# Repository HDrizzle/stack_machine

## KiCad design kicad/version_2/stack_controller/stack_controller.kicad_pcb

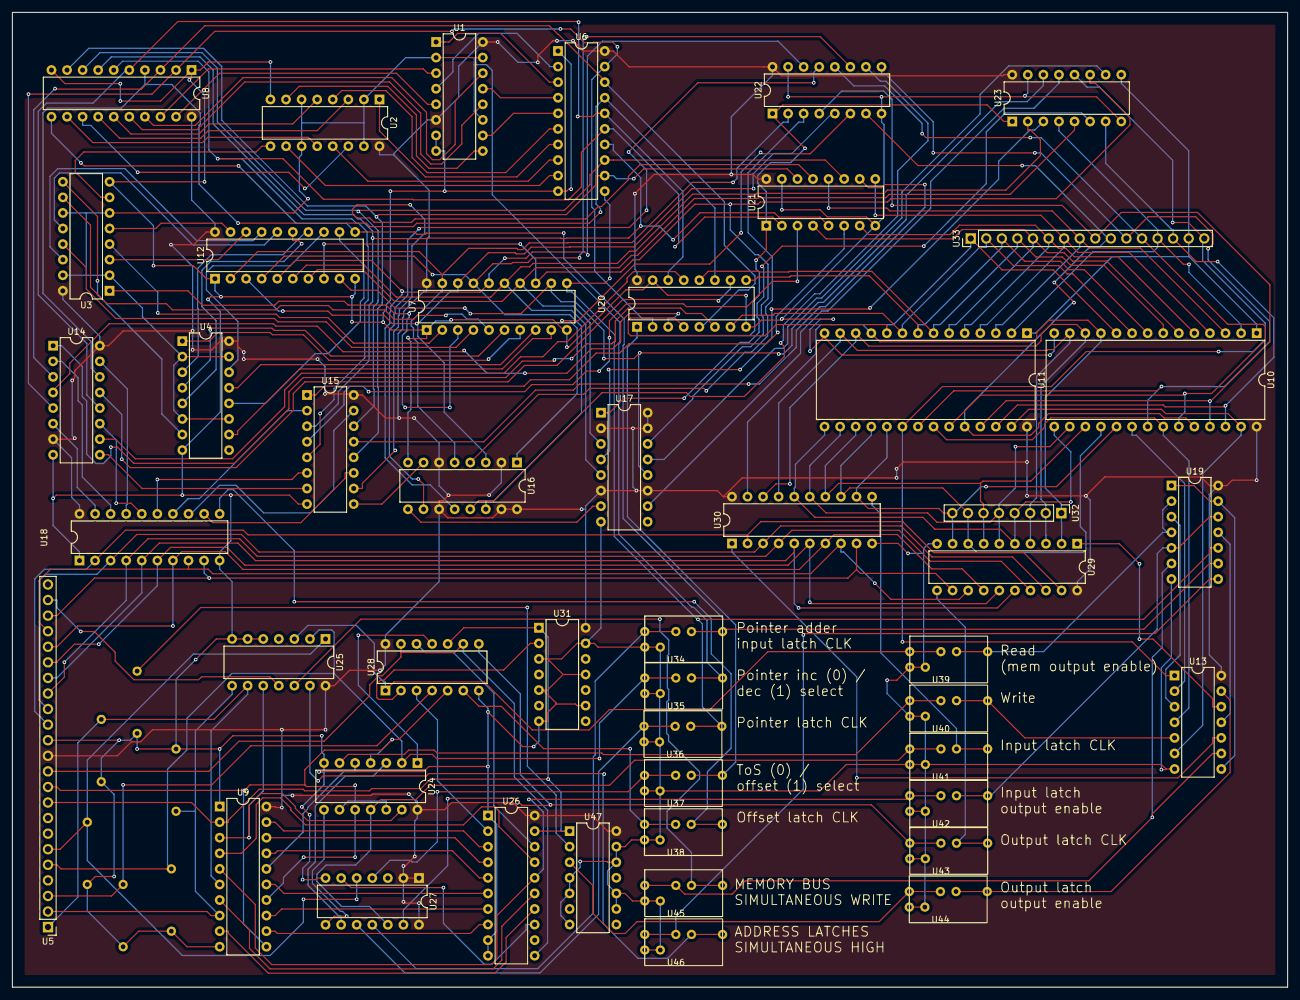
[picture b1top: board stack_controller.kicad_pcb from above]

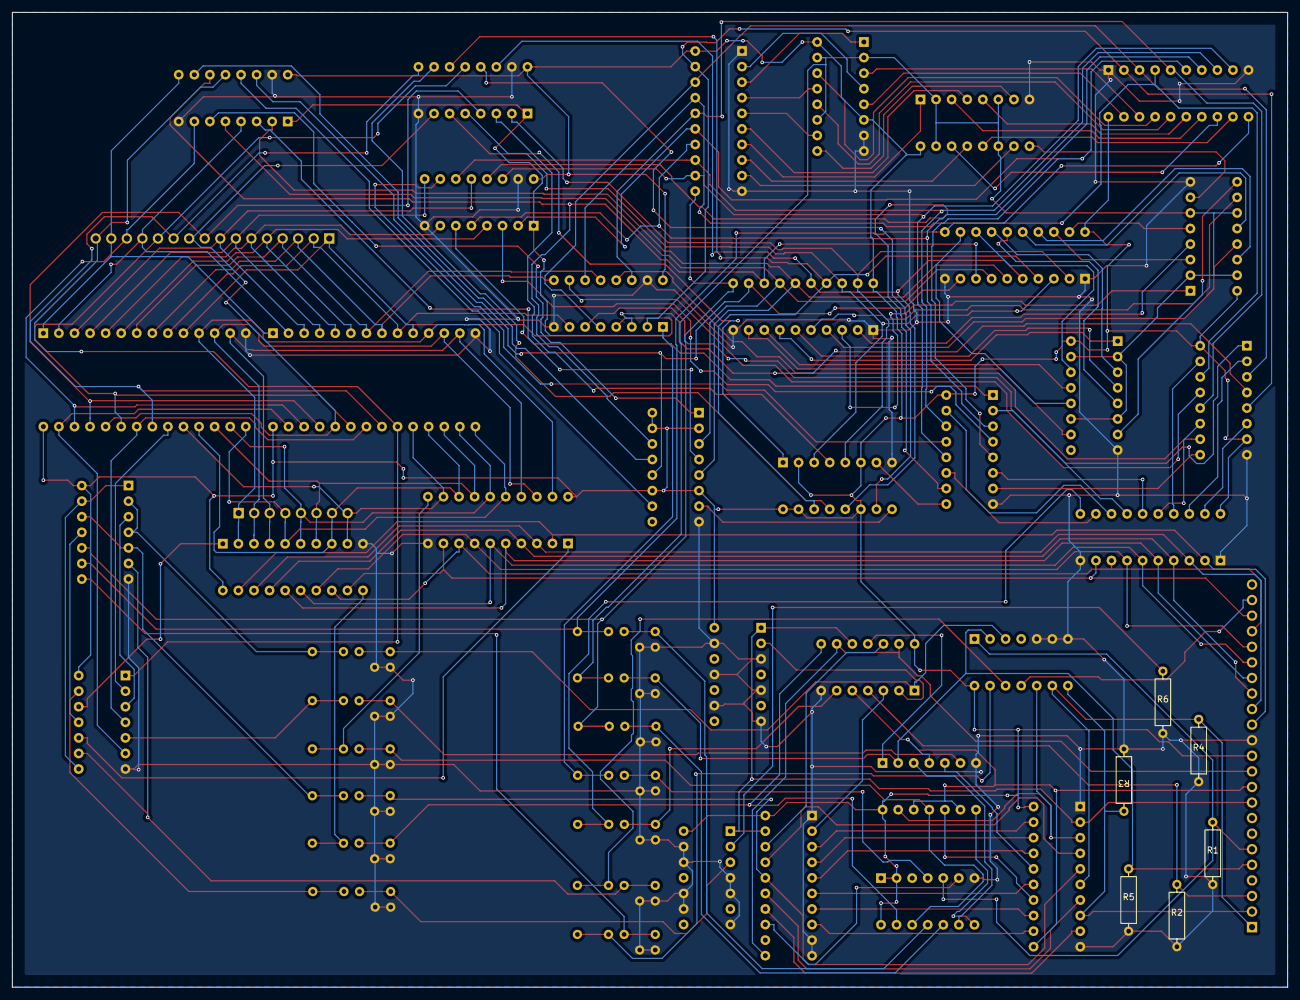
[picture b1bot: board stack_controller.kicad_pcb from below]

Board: 2 copper layers, 208.0 x 159.0 mm, 53 parts (6 on the bottom side), 174 nets.

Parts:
R1, R2, R3, R4, R5, R6: 1k; 0.4_pitch_resistor
U1, U2, U3, U4, U14, U15, U16, U17, U20, U21, U22, U23: DIP-16_W7.62mm
U5: PinHeader_1x23_P2.54mm_Vertical
U6, U7, U8, U9, U12, U18, U26, U29, U30: DIP-20_W7.62mm
U10, U11: DIP-28_W15.24mm
U13, U19, U24, U25, U27, U28, U31, U47: DIP-14_W7.62mm
U32: PinHeader_1x08_P2.54mm_Vertical
U33: PinHeader_1x16_P2.54mm_Vertical
U34, U35, U36, U37, U38, U39, U40, U41, U42, U43, U44, U45, U46: jumper

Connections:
unnamed: U1.5 (A0), U8.19 (Q0)
unnamed: U1.3 (A1), U8.18 (Q1)
unnamed: U1.14 (A2), U8.17 (Q2)
unnamed: U1.12 (A3), U8.16 (Q3)
unnamed: U1.6 (B0), U1.16 (V+), U2.16 (V+), U3.16 (V+), U4.16 (V+), U5.12 (V+), U6.20 (V+), U7.20 (V+), U8.20 (V+), U9.20 (V+), U10.28 (V+), U11.28 (V+), U12.20 (V+), U13.14 (V+), U14.7 (C_IN), U14.16 (V+), U15.16 (V+), U16.2 (B1), U16.6 (B0), U16.11 (B3), U16.15 (B2), U16.16 (V+), U17.2 (B1), U17.6 (B0), U17.11 (B3), U17.15 (B2), U17.16 (V+), U18.20 (V+), U19.14 (V+), U20.16 (V+), U21.16 (V+), U22.16 (V+), U23.16 (V+), U24.14 (V+), U25.14 (V+), U26.20 (V+), U27.1 (0A), U27.2 (0B), U27.14 (V+), U28.14 (V+), U29.20 (V+), U30.20 (V+), U31.14 (V+), U47.14 (V+)
unnamed: U1.2 (B1), U1.11 (B3), U1.15 (B2), U2.2 (B1), U2.6 (B0), U2.11 (B3), U2.15 (B2), U3.2 (B1), U3.6 (B0), U3.11 (B3), U3.15 (B2), U4.2 (B1), U4.6 (B0), U4.11 (B3), U4.15 (B2), U35.3 (OUT)
unnamed: R1.2, R2.2, R3.2, R4.2, R5.2, R6.2, U1.7 (C_IN), U1.8 (GND), U2.8 (GND), U3.8 (GND), U4.8 (GND), U5.13 (GND), U6.1 (OE#), U6.10 (GND), U7.1 (OE#), U7.10 (GND), U8.1 (OE#), U8.10 (GND), U9.1 (OE#), U9.10 (GND), U10.14 (GND), U11.14 (GND), U12.1 (OE#), U12.10 (GND), U13.7 (GND), U14.8 (GND), U15.8 (GND), U16.8 (GND), U17.8 (GND), U18.1 (OE#), U18.10 (GND), U19.7 (GND), U20.8 (GND), U20.15 (OE#), U21.8 (GND), U21.15 (OE#), U22.8 (GND), U22.15 (OE#), U23.8 (GND), U23.15 (OE#), U24.7 (GND), U25.5 (1A), U25.6 (1B), U25.7 (GND), U26.1 (OE#), U26.9 (D7), U26.10 (GND), U27.7 (GND), U28.7 (GND), U29.10 (GND), U30.10 (GND), U31.3 (I1), U31.5 (I2), U31.7 (GND), U31.9 (I3), U31.11 (I4), U31.13 (I5), U34.2 (GND), U35.2 (GND), U36.2 (GND), U37.2 (GND), U38.2 (GND), U39.2 (GND), U40.2 (GND), U41.2 (GND), U42.2 (GND), U43.2 (GND), U44.2 (GND), U45.2 (GND), U46.2 (GND), U47.4 (2A), U47.5 (2B), U47.7 (GND), U47.9 (4B), U47.10 (4A), U47.12 (3B), U47.13 (3A)
unnamed: U1.9 (C_OUT), U2.7 (C_IN)
unnamed: U1.4 (Σ0), U6.2 (D0)
unnamed: U1.1 (Σ1), U6.3 (D1)
unnamed: U1.13 (Σ2), U6.4 (D2)
unnamed: U1.10 (Σ3), U6.5 (D3)
unnamed: U2.5 (A0), U8.15 (Q4)
unnamed: U2.3 (A1), U8.14 (Q5)
unnamed: U2.14 (A2), U8.13 (Q6)
unnamed: U2.12 (A3), U8.12 (Q7)
unnamed: U2.9 (C_OUT), U3.7 (C_IN)
unnamed: U2.4 (Σ0), U6.6 (D4)
unnamed: U2.1 (Σ1), U6.7 (D5)
unnamed: U2.13 (Σ2), U6.8 (D6)
unnamed: U2.10 (Σ3), U6.9 (D7)
unnamed: U3.9 (C_OUT), U4.7 (C_IN)
unnamed: U3.4 (Σ0), U7.2 (D0)
unnamed: U3.1 (Σ1), U7.3 (D1)
unnamed: U3.13 (Σ2), U7.4 (D2)
unnamed: U3.10 (Σ3), U7.5 (D3)
unnamed: U4.4 (Σ0), U7.6 (D4)
unnamed: U4.1 (Σ1), U7.7 (D5)
unnamed: U4.13 (Σ2), U7.8 (D6)
unnamed: U4.10 (Σ3), U7.9 (D7)
unnamed: U10.10 (A0), U11.10 (A0), U20.4 (Q0), U33.1 (0)
unnamed: U10.9 (A1), U11.9 (A1), U20.7 (Q1), U33.2 (1)
unnamed: U10.8 (A2), U11.8 (A2), U20.9 (Q2), U33.3 (2)
unnamed: U10.7 (A3), U11.7 (A3), U20.12 (Q3), U33.4 (3)
unnamed: U10.6 (A4), U11.6 (A4), U21.4 (Q0), U33.5 (4)
unnamed: U10.5 (A5), U11.5 (A5), U21.7 (Q1), U33.6 (5)
unnamed: U10.4 (A6), U11.4 (A6), U21.9 (Q2), U33.7 (6)
unnamed: U10.3 (A7), U11.3 (A7), U21.12 (Q3), U33.8 (7)
unnamed: U10.25 (A8), U11.25 (A8), U22.4 (Q0), U33.9 (8)
unnamed: U10.24 (A9), U11.24 (A9), U22.7 (Q1), U33.10 (9)
unnamed: U10.21 (A10), U11.21 (A10), U22.9 (Q2), U33.11 (10)
unnamed: U10.23 (A11), U11.23 (A11), U22.12 (Q3), U33.12 (11)
unnamed: U10.2 (A12), U11.2 (A12), U23.4 (Q0), U33.13 (12)
unnamed: U10.26 (A13), U11.26 (A13), U23.7 (Q1), U33.14 (13)
unnamed: U10.1 (A14), U11.1 (A14), U23.9 (Q2), U33.15 (14)
unnamed: U10.20 (CE#), U13.2 (O0)
unnamed: U10.11 (D0), U11.11 (D0), U29.2 (D0), U30.19 (Q0), U32.1 (0)
unnamed: U10.12 (D1), U11.12 (D1), U29.3 (D1), U30.18 (Q1), U32.2 (1)
unnamed: U10.13 (D2), U11.13 (D2), U29.4 (D2), U30.17 (Q2), U32.3 (2)
unnamed: U10.15 (D3), U11.15 (D3), U29.5 (D3), U30.16 (Q3), U32.4 (3)
unnamed: U10.16 (D4), U11.16 (D4), U29.6 (D4), U30.15 (Q4), U32.5 (4)
unnamed: U10.17 (D5), U11.17 (D5), U29.7 (D5), U30.14 (Q5), U32.6 (5)
unnamed: U10.18 (D6), U11.18 (D6), U29.8 (D6), U30.13 (Q6), U32.7 (6)
unnamed: U10.19 (D7), U11.19 (D7), U29.9 (D7), U30.12 (Q7), U32.8 (7)
unnamed: U10.22 (OE#), U11.22 (OE#), U13.4 (O1)
unnamed: U10.27 (WE#), U11.27 (WE#), U13.6 (O2)
unnamed: U11.20 (CE#), U13.1 (I0), U23.12 (Q3), U33.16 (15)
unnamed: U8.11 (CLK), U12.11 (CLK), U19.9 (4B), U34.3 (OUT)
unnamed: U7.19 (Q0), U12.2 (D0), U16.5 (A0), U22.2 (A0)
unnamed: U7.18 (Q1), U12.3 (D1), U16.3 (A1), U22.5 (A1)
unnamed: U7.17 (Q2), U12.4 (D2), U16.14 (A2), U22.11 (A2)
unnamed: U7.16 (Q3), U12.5 (D3), U16.12 (A3), U22.14 (A3)
unnamed: U7.15 (Q4), U12.6 (D4), U17.5 (A0), U23.2 (A0)
unnamed: U7.14 (Q5), U12.7 (D5), U17.3 (A1), U23.5 (A1)
unnamed: U7.13 (Q6), U12.8 (D6), U17.14 (A2), U23.11 (A2)
unnamed: U7.12 (Q7), U12.9 (D7), U17.12 (A3), U23.14 (A3)
unnamed: U3.5 (A0), U12.19 (Q0)
unnamed: U3.3 (A1), U12.18 (Q1)
unnamed: U3.14 (A2), U12.17 (Q2)
unnamed: U3.12 (A3), U12.16 (Q3)
unnamed: U4.5 (A0), U12.15 (Q4)
unnamed: U4.3 (A1), U12.14 (Q5)
unnamed: U4.14 (A2), U12.13 (Q6)
unnamed: U4.12 (A3), U12.12 (Q7)
unnamed: U13.8 (03), U19.1 (1A), U19.13 (3A)
unnamed: U13.3 (I1), U19.3 (1Q)
unnamed: U13.5 (I2), U40.3 (OUT)
unnamed: U13.9 (I3), U19.6 (2Q), U45.1 (IN)
unnamed: U13.11 (I4), U19.11 (3Q)
unnamed: U13.13 (I5), U44.3 (OUT)
unnamed: U13.10 (O4), U30.1 (OE#)
unnamed: U13.12 (O5), U29.1 (OE#)
unnamed: U6.19 (Q0), U8.2 (D0), U14.5 (A0), U20.2 (A0)
unnamed: U6.18 (Q1), U8.3 (D1), U14.3 (A1), U20.5 (A1)
unnamed: U6.17 (Q2), U8.4 (D2), U14.14 (A2), U20.11 (A2)
unnamed: U6.16 (Q3), U8.5 (D3), U14.12 (A3), U20.14 (A3)
unnamed: U14.6 (B0), U18.19 (Q0)
unnamed: U14.2 (B1), U18.18 (Q1)
unnamed: U14.15 (B2), U18.17 (Q2)
unnamed: U14.11 (B3), U18.16 (Q3)
unnamed: U14.9 (C_OUT), U15.7 (C_IN)
unnamed: U14.4 (Σ0), U20.3 (B0)
unnamed: U14.1 (Σ1), U20.6 (B1)
unnamed: U14.13 (Σ2), U20.10 (B2)
unnamed: U14.10 (Σ3), U20.13 (B3)
unnamed: U6.15 (Q4), U8.6 (D4), U15.5 (A0), U21.2 (A0)
unnamed: U6.14 (Q5), U8.7 (D5), U15.3 (A1), U21.5 (A1)
unnamed: U6.13 (Q6), U8.8 (D6), U15.14 (A2), U21.11 (A2)
unnamed: U6.12 (Q7), U8.9 (D7), U15.12 (A3), U21.14 (A3)
unnamed: U15.6 (B0), U18.15 (Q4)
unnamed: U15.2 (B1), U18.14 (Q5)
unnamed: U15.15 (B2), U18.13 (Q6)
unnamed: U15.11 (B3), U18.12 (Q7)
unnamed: U15.9 (C_OUT), U16.7 (C_IN)
unnamed: U15.4 (Σ0), U21.3 (B0)
unnamed: U15.1 (Σ1), U21.6 (B1)
unnamed: U15.13 (Σ2), U21.10 (B2)
unnamed: U15.10 (Σ3), U21.13 (B3)
unnamed: U16.9 (C_OUT), U17.7 (C_IN)
unnamed: U16.4 (Σ0), U22.3 (B0)
unnamed: U16.1 (Σ1), U22.6 (B1)
unnamed: U16.13 (Σ2), U22.10 (B2)
unnamed: U16.10 (Σ3), U22.13 (B3)
unnamed: U17.4 (Σ0), U23.3 (B0)
unnamed: U17.1 (Σ1), U23.6 (B1)
unnamed: U17.13 (Σ2), U23.10 (B2)
unnamed: U17.10 (Σ3), U23.13 (B3)
unnamed: U18.11 (CLK), U38.3 (OUT)
unnamed: U5.14 (D0), U18.2 (D0), U29.19 (Q0), U30.2 (D0)
unnamed: U5.15 (D1), U18.3 (D1), U29.18 (Q1), U30.3 (D1)
unnamed: U5.16 (D2), U18.4 (D2), U29.17 (Q2), U30.4 (D2)
unnamed: U5.17 (D3), U18.5 (D3), U29.16 (Q3), U30.5 (D3)
unnamed: U5.18 (D4), U18.6 (D4), U29.15 (Q4), U30.6 (D4)
unnamed: U5.19 (D5), U18.7 (D5), U29.14 (Q5), U30.7 (D5)
unnamed: U5.20 (D6), U18.8 (D6), U29.13 (Q6), U30.8 (D6)
unnamed: U5.21 (D7), U18.9 (D7), U29.12 (Q7), U30.9 (D7)
unnamed: U19.2 (1B), U19.4 (2A), U39.3 (OUT)
unnamed: U19.5 (2B), U19.12 (3B), U42.3 (OUT)
unnamed: U6.11 (CLK), U7.11 (CLK), U19.10 (4A), U36.3 (OUT)
unnamed: U19.8 (4Q), U46.1 (IN)
unnamed: U20.1 (S), U21.1 (S), U22.1 (S), U23.1 (S), U37.3 (OUT)
unnamed: U24.1 (1A), U28.11 (3Q)
unnamed: R5.1, U5.5 (WRITE_0), U24.2 (1B), U25.2 (0B), U35.1 (IN)
unnamed: U24.3 (1Q), U27.9 (2B)
unnamed: U5.10 (CLK_A), U9.11 (CLK), U24.4 (2A), U24.9 (4B), U24.12 (3B), U28.5 (2B)
unnamed: U9.16 (Q3), U24.5 (2B)
unnamed: U24.6 (2Q), U40.1 (IN)
unnamed: U9.3 (D1), U24.13 (3A), U25.10 (Q2)
unnamed: U24.11 (3Q), U27.12 (3A), U41.1 (IN)
unnamed: U9.14 (Q5), U24.10 (4A)
unnamed: U24.8 (4Q), U27.8 (2A)
unnamed: R1.1, U5.6 (WRITE_1), U25.1 (0A), U27.5 (1A)
unnamed: R3.1, U5.2 (READ_1), U9.8 (D6), U25.8 (2A)
unnamed: R4.1, U5.1 (READ_0), U9.6 (D4), U25.9 (2B)
unnamed: U25.12 (3A), U45.3 (OUT)
unnamed: U25.13 (3B), U46.3 (OUT)
unnamed: U25.3 (Q0), U28.1 (1A), U39.1 (IN)
unnamed: U5.22 (FAULT), U25.11 (Q3)
unnamed: U5.11 (CLK_B), U26.11 (CLK), U28.9 (4B), U28.13 (3A)
unnamed: U26.2 (D0), U28.3 (1Q)
unnamed: U9.19 (Q0), U26.3 (D1)
unnamed: U9.18 (Q1), U26.4 (D2)
unnamed: U9.17 (Q2), U26.5 (D3)
unnamed: U9.15 (Q4), U26.6 (D4)
unnamed: U9.13 (Q6), U26.7 (D5)
unnamed: U9.12 (Q7), U26.8 (D6)
unnamed: U5.9 (READ_READY), U9.2 (D0), U26.19 (Q0), U28.10 (4A), U31.1 (I0), U47.1 (1A)
unnamed: U26.18 (Q1), U28.12 (3B)
unnamed: U9.4 (D2), U26.17 (Q2)
unnamed: U9.5 (D3), U26.16 (Q3), U42.1 (IN)
unnamed: U9.7 (D5), U26.15 (Q4)
unnamed: U9.9 (D7), U26.14 (Q5)
unnamed: U26.13 (Q6), U27.6 (1B)
unnamed: U27.13 (3B), U28.8 (4Q), U43.1 (IN)
unnamed: U27.4 (Q1), U37.1 (IN)
unnamed: U27.10 (Q2), U36.1 (IN)
unnamed: U27.11 (Q3), U34.1 (IN)
unnamed: U28.2 (1B), U31.2 (O0)
unnamed: R2.1, U5.3 (READ_2), U28.4 (2A)
unnamed: U28.6 (2Q), U38.1 (IN)
unnamed: U29.11 (CLK), U43.3 (OUT)
unnamed: U30.11 (CLK), U41.3 (OUT)
unnamed: U44.1 (IN), U47.3 (1Q)
unnamed: R6.1, U47.2 (1B)
